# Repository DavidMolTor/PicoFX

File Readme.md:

# PICO FX

A simple stereo guitar effects platform using an RP Pico 2 development board.

## Introduction

This module is designed to be used as a development platform for guitar effects running on the RP2350 architecture.

The module contains a CS4272 codec with stereo inputs and outputs. It also includes a set of clean buffers to match the guitar and other effects in the chain.

All the power regulation is done through LDO regulators that prioritize low ripple in exchange for worse efficiency.

It is designed to work with 9V intput voltage. It also has a set of headers for it to be able to interface with a control board in the future.

## Features

 - Clear separation between digital and analog sections.

 - Steareo input and output.

 - Clean voltage delivery.

 - Flexible interface for controls.

 - Easy future development.

 - Afforable BOM.

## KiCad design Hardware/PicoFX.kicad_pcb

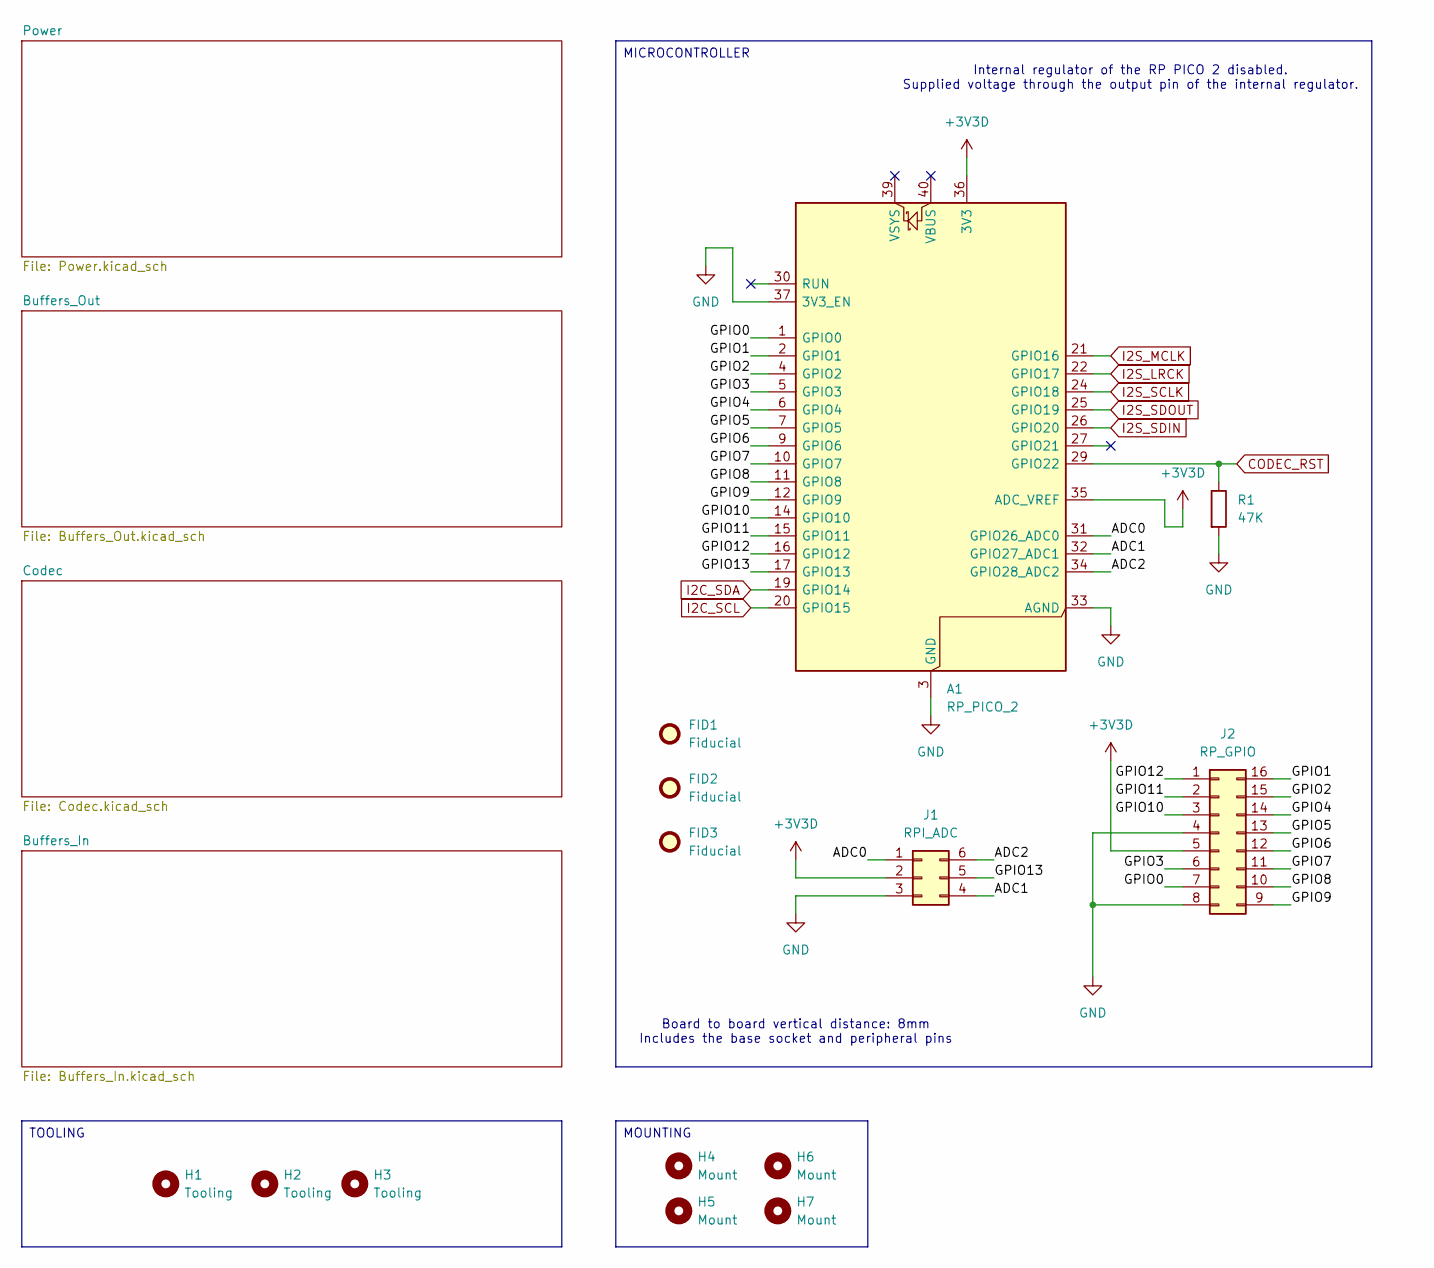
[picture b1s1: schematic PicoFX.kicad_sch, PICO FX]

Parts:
A1: RP_PICO_2; RP_PICO_2_SMD; Manufacturer Part Pico 2; JLCPCB Part C41407547
FID1, FID2, FID3: Fiducial; Fiducial_0.75mm_Mask1.5mm
H1, H2, H3: Tooling; ToolingHole_1.152mm
H4, H5, H6, H7: Mount; MountingHole_2.2mm_M2
J1: RPI_ADC; HEADER_THROUGH_2x03_P2.54mm; Manufacturer Part HC-PM254-5.0H-2x3PS-02A; JLCPCB Part C42163131
J2: RP_GPIO; HEADER_THROUGH_2x08_P2.54mm; Manufacturer Part HC-PM254-5.0H-2x8PS; JLCPCB Part C42163136
R1: 47K; R_0603_1608Metric; Manufacturer Part 0603WAF4702T5E; JLCPCB Part C25819

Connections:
+3V3D: A1.35 (ADC_VREF), A1.36 (3V3), J1.2, J2.5; also elsewhere on the board
/ADC0: A1.31 (GPIO26_ADC0), J1.1
/ADC1: A1.32 (GPIO27_ADC1), J1.4
/ADC2: A1.34 (GPIO28_ADC2), J1.6
/GPIO0: A1.1 (GPIO0), J2.7
/GPIO1: A1.2 (GPIO1), J2.16
/GPIO2: A1.4 (GPIO2), J2.15
/GPIO3: A1.5 (GPIO3), J2.6
/GPIO4: A1.6 (GPIO4), J2.14
/GPIO5: A1.7 (GPIO5), J2.13
/GPIO6: A1.9 (GPIO6), J2.12
/GPIO7: A1.10 (GPIO7), J2.11
/GPIO8: A1.11 (GPIO8), J2.10
/GPIO9: A1.12 (GPIO9), J2.9
/GPIO10: A1.14 (GPIO10), J2.3
/GPIO11: A1.15 (GPIO11), J2.2
/GPIO12: A1.16 (GPIO12), J2.1
/GPIO13: A1.17 (GPIO13), J1.5
CODEC_RST: A1.29 (GPIO22), R1.1; also elsewhere on the board
GND: A1.3 (GND), A1.8 (GND), A1.13 (GND), A1.18 (GND), A1.23 (GND), A1.28 (GND), A1.33 (AGND), A1.37 (3V3_EN), A1.38 (GND), J1.3, J2.4, J2.8, R1.2; also elsewhere on the board
I2C_SCL: A1.20 (GPIO15); also elsewhere on the board
I2C_SDA: A1.19 (GPIO14); also elsewhere on the board
I2S_LRCK: A1.22 (GPIO17); also elsewhere on the board
I2S_MCLK: A1.21 (GPIO16); also elsewhere on the board
I2S_SCLK: A1.24 (GPIO18); also elsewhere on the board
I2S_SDIN: A1.26 (GPIO20); also elsewhere on the board
I2S_SDOUT: A1.25 (GPIO19); also elsewhere on the board

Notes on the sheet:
Board to board vertical distance: 8mm Includes the base socket and peripheral pins
Internal regulator of the RP PICO 2 disabled. Supplied voltage through the output pin of the internal regulator.
MICROCONTROLLER
TOOLING
MOUNTING

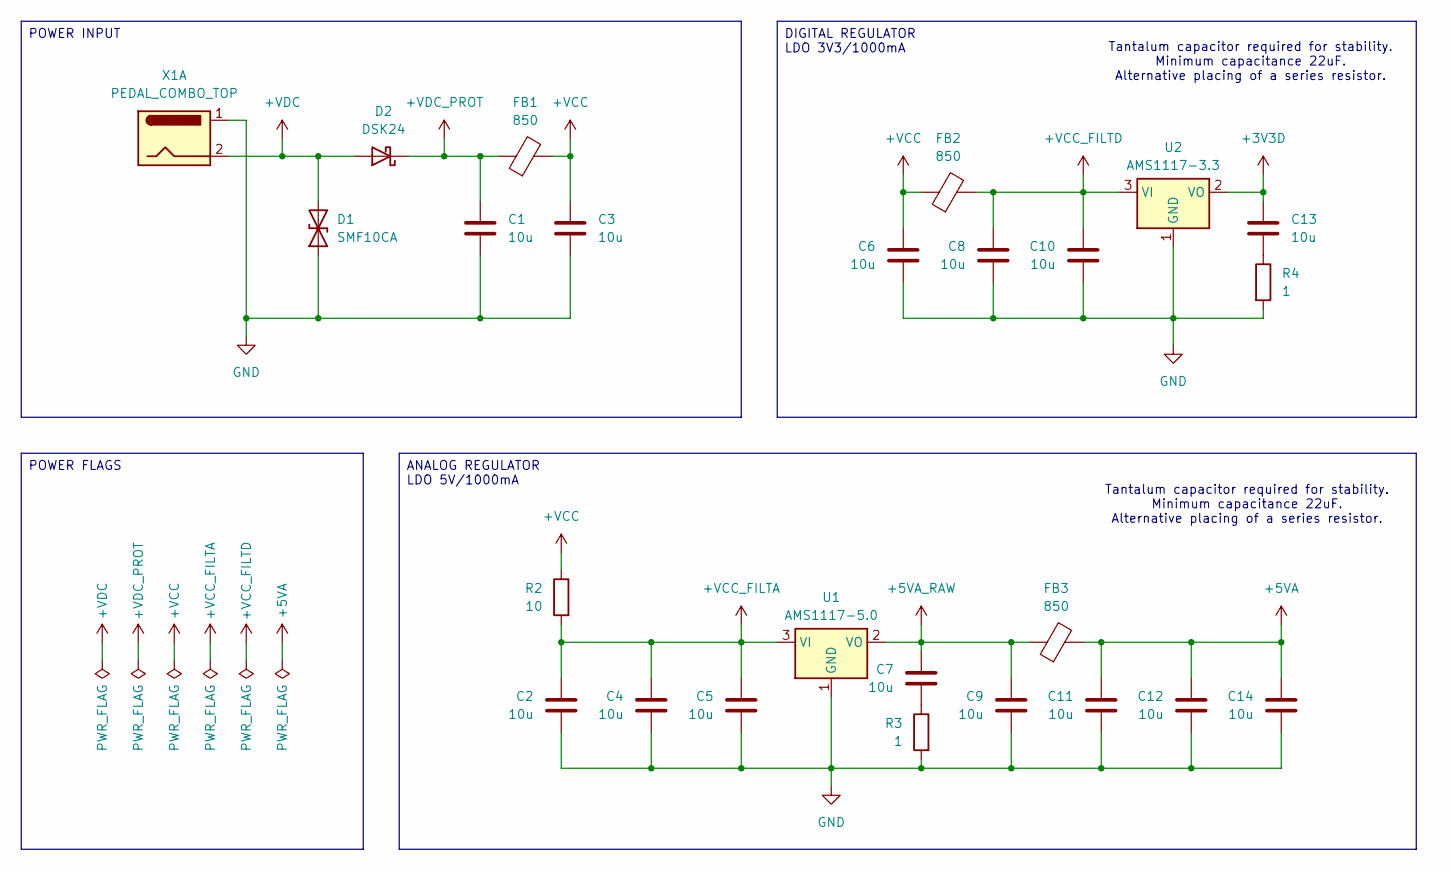
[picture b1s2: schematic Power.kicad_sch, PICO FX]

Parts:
C1, C2, C3, C4, C5, C6, C7, C8, C9, C10, C11, C12, C13, C14: 10u; C_0805_2012Metric; Manufacturer Part CL21A106KAYNNNE; JLCPCB Part C15850
D1: SMF10CA; D_SOD-123F; Manufacturer Part SMF10CA; JLCPCB Part C19077505
D2: DSK24; D_SOD-123F; Manufacturer Part DSK24; JLCPCB Part C22466352
FB1, FB2, FB3: 850; L_0603_1608Metric; Manufacturer Part SDCL1608C68NJTDF; JLCPCB Part C13415
R2: 10; R_0603_1608Metric; Manufacturer Part 0603WAF100JT5E; JLCPCB Part C22859
R3, R4: 1; R_0603_1608Metric; Manufacturer Part 0603WAF100KT5E; JLCPCB Part C22936
U1: AMS1117-5.0; SOT-223-3_TabPin2; Manufacturer Part AMS1117-5.0; JLCPCB Part C6187
U2: AMS1117-3.3; SOT-223-3_TabPin2; Manufacturer Part AMS1117-3.3; JLCPCB Part C6186
X1: PEDAL_COMBO_TOP

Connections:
+3V3D: C13.1, U2.2 (VO); also elsewhere on the board
+5VA: C11.1, C12.1, C14.1, FB3.2; also elsewhere on the board
+5VA_RAW: C7.1, C9.1, FB3.1, U1.2 (VO)
+VCC: C3.1, C6.1, FB1.2, FB2.1, R2.1
+VCC_FILTA: C2.1, C4.1, C5.1, R2.2, U1.3 (VI)
+VCC_FILTD: C8.1, C10.1, FB2.2, U2.3 (VI)
+VDC: D1.2 (A2), D2.2 (A), X1.2
+VDC_PROT: C1.1, D2.1 (K), FB1.1
GND: C1.2, C2.2, C3.2, C4.2, C5.2, C6.2, C8.2, C9.2, C10.2, C11.2, C12.2, C14.2, D1.1 (A1), R3.2, R4.2, U1.1 (GND), U2.1 (GND), X1.1; also elsewhere on the board
unnamed: C7.2, R3.1
unnamed: C13.2, R4.1

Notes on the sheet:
Tantalum capacitor required for stability. Minimum capacitance 22uF. Alternative placing of a series resistor.
DIGITAL REGULATOR LDO 3V3/1000mA
POWER INPUT
ANALOG REGULATOR LDO 5V/1000mA
POWER FLAGS

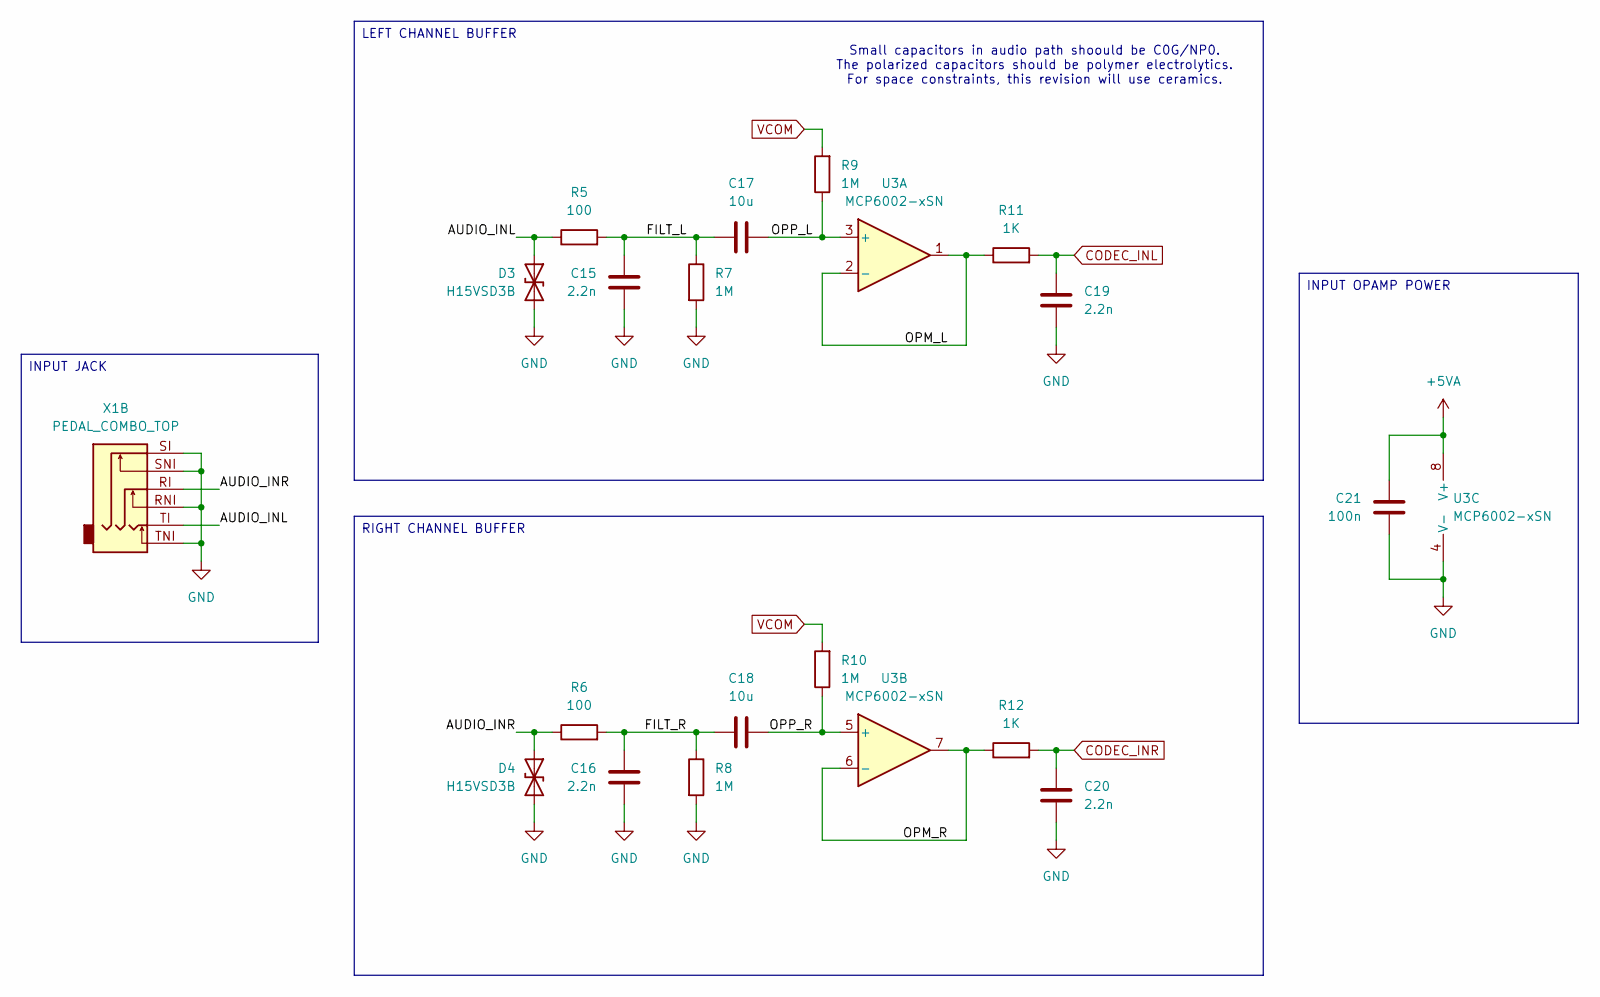
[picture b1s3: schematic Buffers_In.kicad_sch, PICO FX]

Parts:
C15, C16, C19, C20: 2.2n; C_0805_2012Metric; Manufacturer Part CL21C222JBFNNNE; JLCPCB Part C28260
C17, C18: 10u; C_0805_2012Metric; Manufacturer Part CL21A106KAYNNNE; JLCPCB Part C15850
C21: 100n; C_0603_1608Metric; Manufacturer Part CC0603KRX7R9BB104; JLCPCB Part C14663
D3, D4: H15VSD3B; D_SOD-323; Manufacturer Part H15VSD3B; JLCPCB Part C20615814
R5, R6: 100; R_0603_1608Metric; Manufacturer Part 0603WAF1000T5E; JLCPCB Part C22775
R7, R8, R9, R10: 1M; R_0603_1608Metric; Manufacturer Part 0603WAF1004T5E; JLCPCB Part C22935
R11, R12: 1K; R_0603_1608Metric; Manufacturer Part 0603WAF1001T5E; JLCPCB Part C21190
U3: MCP6002-xSN; SOIC-8_3.9x4.9mm_P1.27mm; Manufacturer Part MCP6002T-I/SN; JLCPCB Part C7377
X1: PEDAL_COMBO_TOP

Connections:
+5VA: C21.1, U3.8 (V+); also elsewhere on the board
/Buffers_In/AUDIO_INL: D3.1 (A1), R5.1, X1.TI
/Buffers_In/AUDIO_INR: D4.1 (A1), R6.1, X1.RI
/Buffers_In/FILT_L: C15.2, C17.1, R5.2, R7.1
/Buffers_In/FILT_R: C16.2, C18.1, R6.2, R8.1
/Buffers_In/OPM_L: R11.1, U3.1, U3.2 (-)
/Buffers_In/OPM_R: R12.1, U3.6 (-), U3.7
/Buffers_In/OPP_L: C17.2, R9.1, U3.3 (+)
/Buffers_In/OPP_R: C18.2, R10.1, U3.5 (+)
CODEC_INL: C19.1, R11.2; also elsewhere on the board
CODEC_INR: C20.1, R12.2; also elsewhere on the board
GND: C15.1, C16.1, C19.2, C20.2, C21.2, D3.2 (A2), D4.2 (A2), R7.2, R8.2, U3.4 (V-), X1.RNI, X1.SI, X1.SNI, X1.TNI; also elsewhere on the board
VCOM: R9.2, R10.2; also elsewhere on the board

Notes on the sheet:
Small capacitors in audio path shoould be C0G/NP0. The polarized capacitors should be polymer electrolytics. For space constraints, this revision will use ceramics.
LEFT CHANNEL BUFFER
INPUT OPAMP POWER
INPUT JACK
RIGHT CHANNEL BUFFER

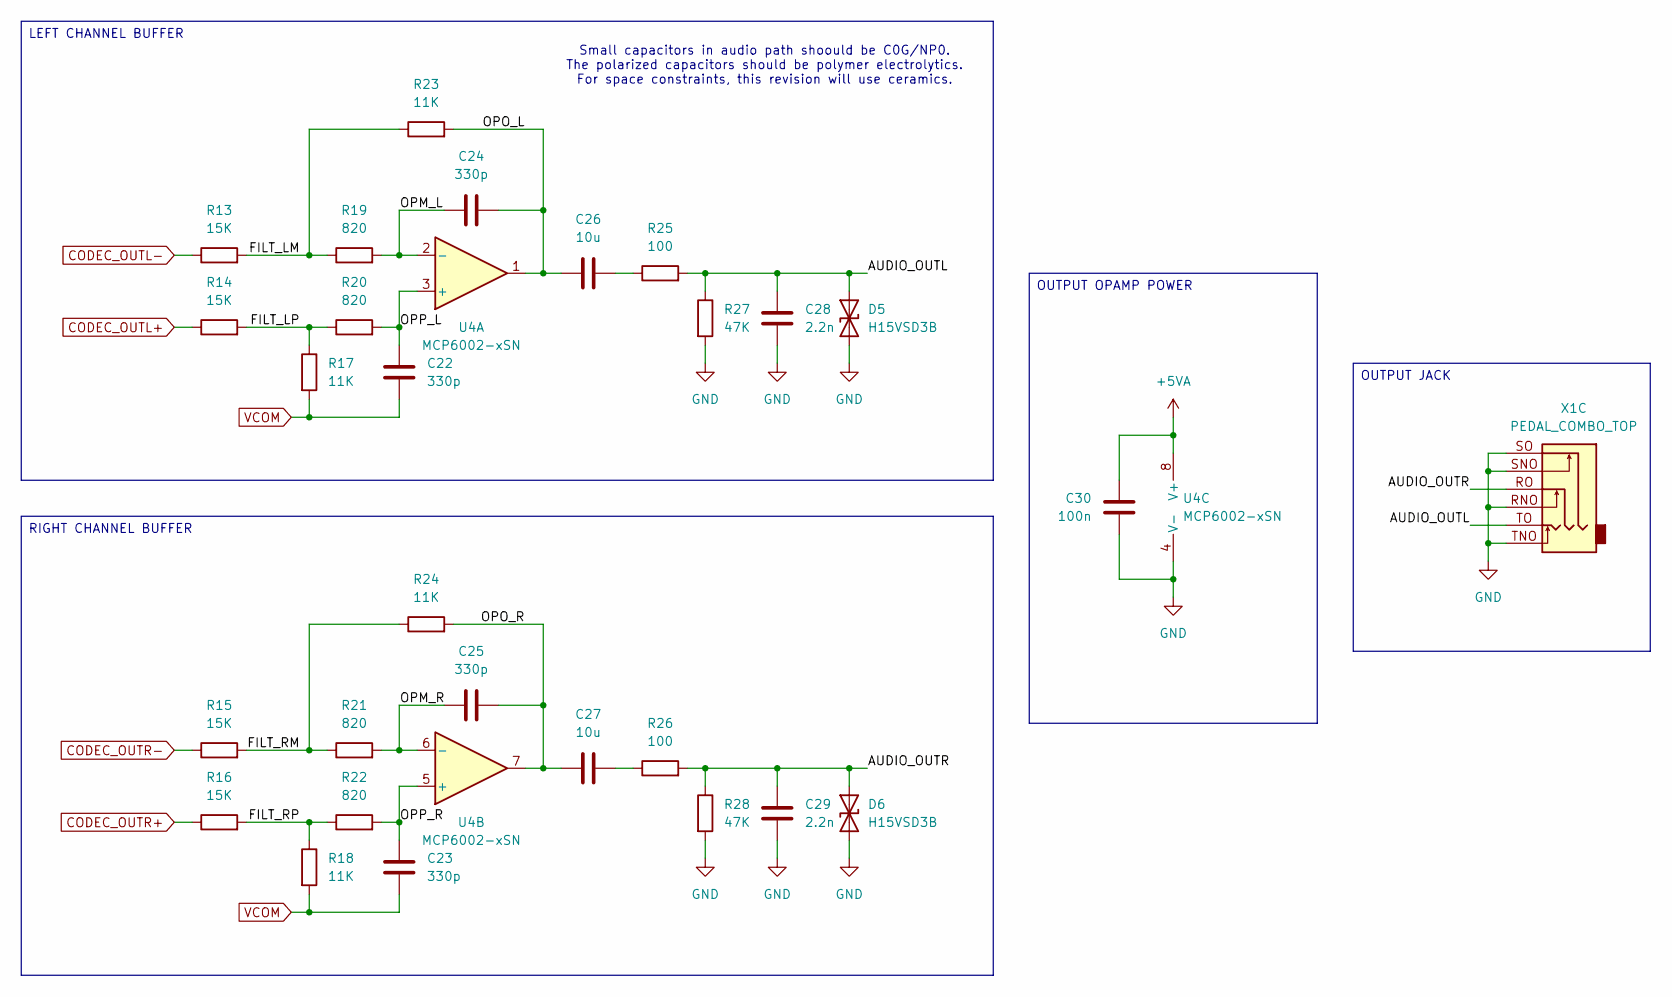
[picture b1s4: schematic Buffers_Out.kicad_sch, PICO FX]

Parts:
C22, C23, C24, C25: 330p; C_0603_1608Metric; Manufacturer Part CL10C331JB8NNNC; JLCPCB Part C1664
C26, C27: 10u; C_0805_2012Metric; Manufacturer Part CL21A106KAYNNNE; JLCPCB Part C15850
C28, C29: 2.2n; C_0805_2012Metric; Manufacturer Part CL21C222JBFNNNE; JLCPCB Part C28260
C30: 100n; C_0603_1608Metric; Manufacturer Part CC0603KRX7R9BB104; JLCPCB Part C14663
D5, D6: H15VSD3B; D_SOD-323; Manufacturer Part H15VSD3B; JLCPCB Part C20615814
R13, R14, R15, R16: 15K; R_0603_1608Metric; Manufacturer Part 0603WAF1502T5E; JLCPCB Part C22809
R17, R18, R23, R24: 11K; R_0603_1608Metric; Manufacturer Part 0603WAF1102T5E; JLCPCB Part C25950
R19, R20, R21, R22: 820; R_0603_1608Metric; Manufacturer Part 0603WAF8200T5E; JLCPCB Part C23253
R25, R26: 100; R_0603_1608Metric; Manufacturer Part 0603WAF1000T5E; JLCPCB Part C22775
R27, R28: 47K; R_0603_1608Metric; Manufacturer Part 0603WAF4702T5E; JLCPCB Part C25819
U4: MCP6002-xSN; SOIC-8_3.9x4.9mm_P1.27mm; Manufacturer Part MCP6002T-I/SN; JLCPCB Part C7377
X1: PEDAL_COMBO_TOP

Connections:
+5VA: C30.1, U4.8 (V+); also elsewhere on the board
/Buffers_Out/AUDIO_OUTL: C28.1, D5.1 (A1), R25.2, R27.1, X1.TO
/Buffers_Out/AUDIO_OUTR: C29.1, D6.1 (A1), R26.2, R28.1, X1.RO
/Buffers_Out/FILT_LM: R13.2, R19.1, R23.1
/Buffers_Out/FILT_LP: R14.2, R17.1, R20.1
/Buffers_Out/FILT_RM: R15.2, R21.1, R24.1
/Buffers_Out/FILT_RP: R16.2, R18.1, R22.1
/Buffers_Out/OPM_L: C24.1, R19.2, U4.2 (-)
/Buffers_Out/OPM_R: C25.1, R21.2, U4.6 (-)
/Buffers_Out/OPO_L: C24.2, C26.1, R23.2, U4.1
/Buffers_Out/OPO_R: C25.2, C27.1, R24.2, U4.7
/Buffers_Out/OPP_L: C22.1, R20.2, U4.3 (+)
/Buffers_Out/OPP_R: C23.1, R22.2, U4.5 (+)
CODEC_OUTL+: R14.1; also elsewhere on the board
CODEC_OUTL-: R13.1; also elsewhere on the board
CODEC_OUTR+: R16.1; also elsewhere on the board
CODEC_OUTR-: R15.1; also elsewhere on the board
GND: C28.2, C29.2, C30.2, D5.2 (A2), D6.2 (A2), R27.2, R28.2, U4.4 (V-), X1.RNO, X1.SNO, X1.SO, X1.TNO; also elsewhere on the board
unnamed: C26.2, R25.1
unnamed: C27.2, R26.1
VCOM: C22.2, C23.2, R17.2, R18.2; also elsewhere on the board

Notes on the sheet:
Small capacitors in audio path shoould be C0G/NP0. The polarized capacitors should be polymer electrolytics. For space constraints, this revision will use ceramics.
OUTPUT JACK
LEFT CHANNEL BUFFER
RIGHT CHANNEL BUFFER
OUTPUT OPAMP POWER

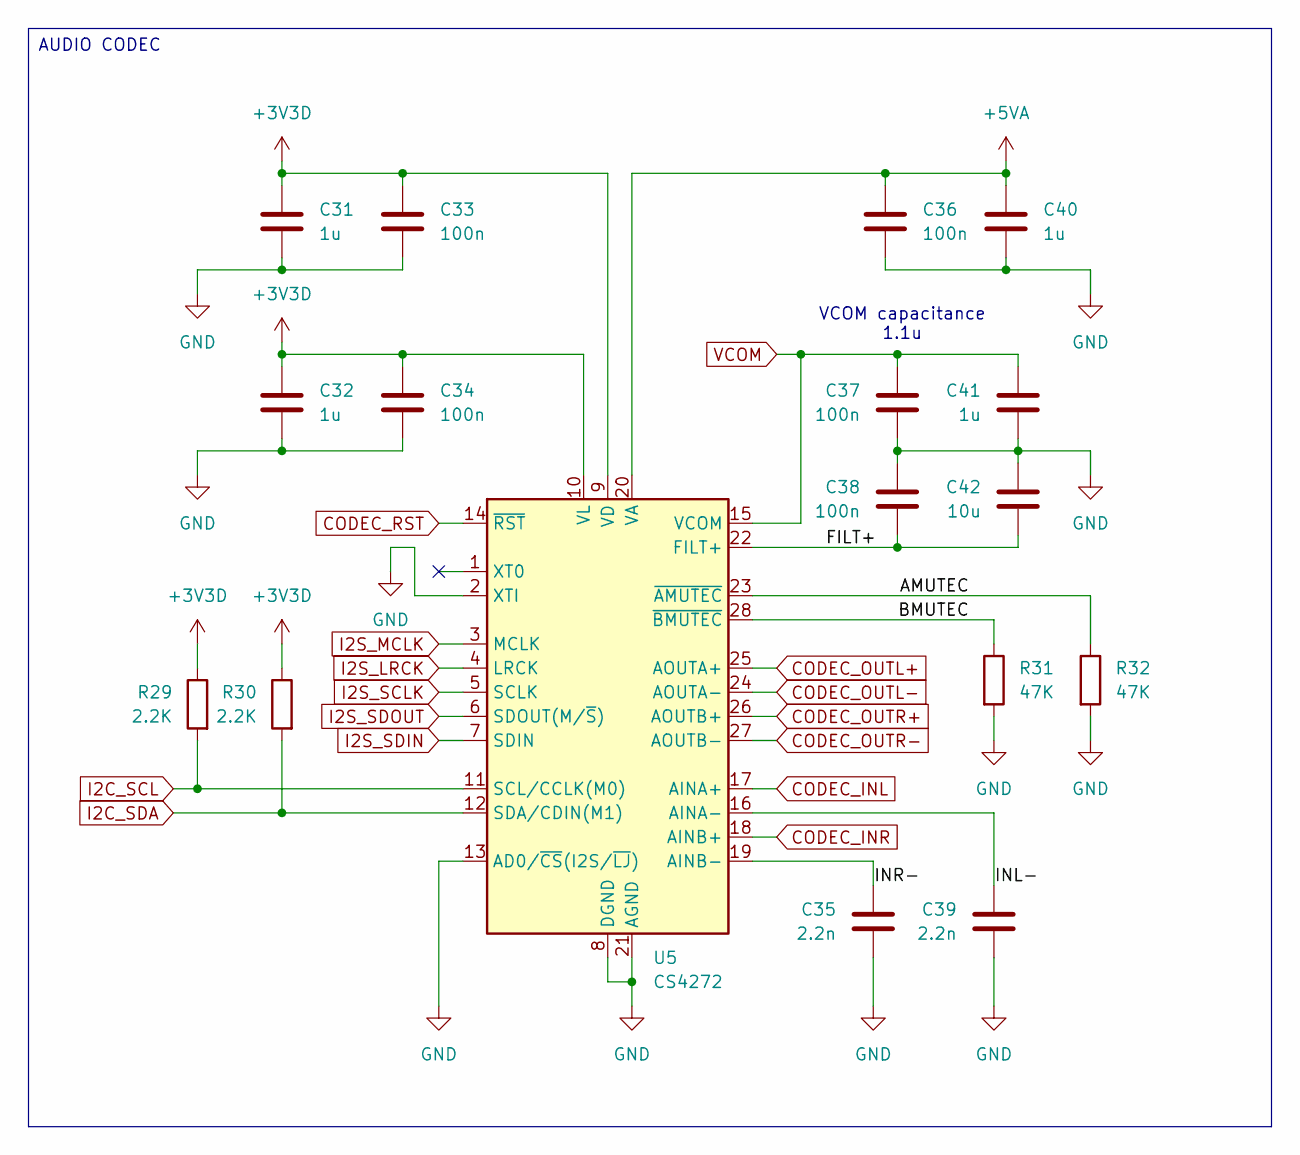
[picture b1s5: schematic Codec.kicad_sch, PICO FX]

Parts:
C31, C32, C40, C41: 1u; C_0805_2012Metric; Manufacturer Part CL21B105KBFNNNE; JLCPCB Part C28323
C33, C34, C36, C37, C38: 100n; C_0603_1608Metric; Manufacturer Part CC0603KRX7R9BB104; JLCPCB Part C14663
C35, C39: 2.2n; C_0805_2012Metric; Manufacturer Part CL21C222JBFNNNE; JLCPCB Part C28260
C42: 10u; C_0805_2012Metric; Manufacturer Part CL21A106KAYNNNE; JLCPCB Part C15850
R29, R30: 2.2K; R_0603_1608Metric; Manufacturer Part 0603WAF2201T5E; JLCPCB Part C4190
R31, R32: 47K; R_0603_1608Metric; Manufacturer Part 0603WAF4702T5E; JLCPCB Part C25819
U5: CS4272; TSSOP-28_4.4x9.7mm_P0.65mm; Manufacturer Part CS4272-CZZR; JLCPCB Part C2151111

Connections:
+3V3D: C31.2, C32.2, C33.1, C34.1, R29.1, R30.1, U5.9 (VD), U5.10 (VL); also elsewhere on the board
+5VA: C36.2, C40.1, U5.20 (VA); also elsewhere on the board
/Codec/AMUTEC: R32.1, U5.23 (~AMUTEC)
/Codec/BMUTEC: R31.1, U5.28 (~BMUTEC)
/Codec/FILT+: C38.1, C42.2, U5.22 (FILT+)
/Codec/INL-: C39.1, U5.16 (AINA-)
/Codec/INR-: C35.1, U5.19 (AINB-)
CODEC_INL: U5.17 (AINA+); also elsewhere on the board
CODEC_INR: U5.18 (AINB+); also elsewhere on the board
CODEC_OUTL+: U5.25 (AOUTA+); also elsewhere on the board
CODEC_OUTL-: U5.24 (AOUTA-); also elsewhere on the board
CODEC_OUTR+: U5.26 (AOUTB+); also elsewhere on the board
CODEC_OUTR-: U5.27 (AOUTB-); also elsewhere on the board
CODEC_RST: U5.14 (~RST); also elsewhere on the board
GND: C31.1, C32.1, C33.2, C34.2, C35.2, C36.1, C37.2, C38.2, C39.2, C40.2, C41.2, C42.1, R31.2, R32.2, U5.2 (XTI), U5.8 (DGND), U5.13 (AD0/~CS(I2S/~LJ)), U5.21 (AGND); also elsewhere on the board
I2C_SCL: R29.2, U5.11 (SCL/CCLK(M0)); also elsewhere on the board
I2C_SDA: R30.2, U5.12 (SDA/CDIN(M1)); also elsewhere on the board
I2S_LRCK: U5.4 (LRCK); also elsewhere on the board
I2S_MCLK: U5.3 (MCLK); also elsewhere on the board
I2S_SCLK: U5.5 (SCLK); also elsewhere on the board
I2S_SDIN: U5.7 (SDIN); also elsewhere on the board
I2S_SDOUT: U5.6 (SDOUT(M/~S)); also elsewhere on the board
VCOM: C37.1, C41.1, U5.15 (VCOM); also elsewhere on the board

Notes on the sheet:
VCOM capacitance 1.1u
AUDIO CODEC

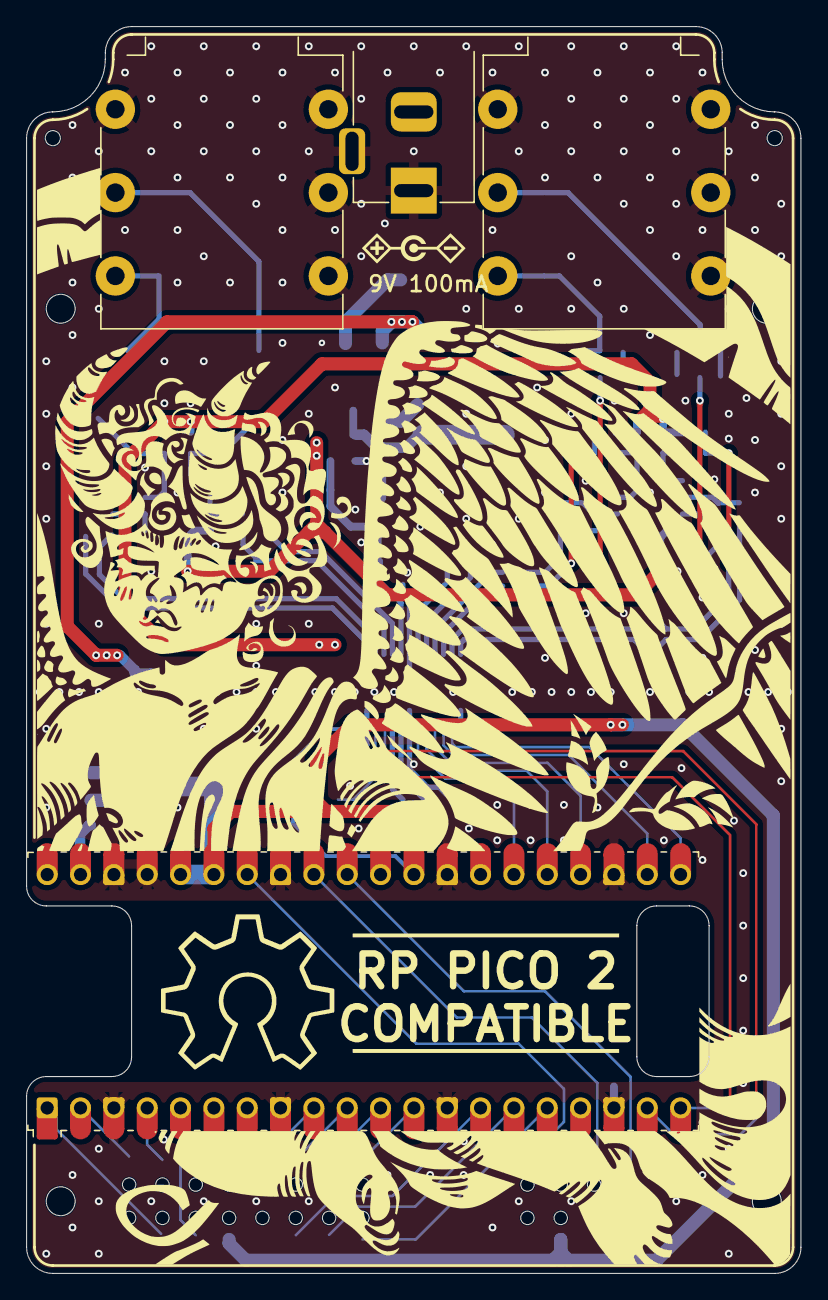
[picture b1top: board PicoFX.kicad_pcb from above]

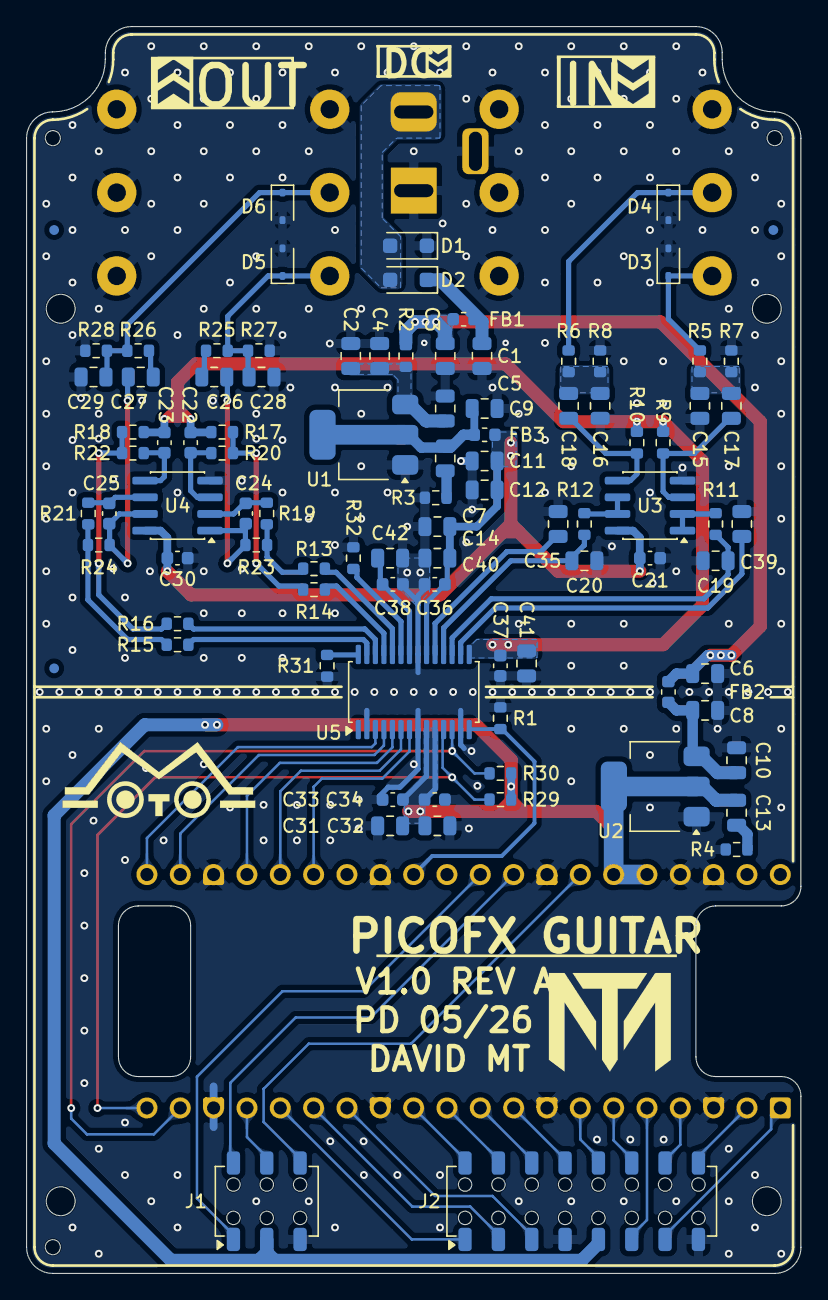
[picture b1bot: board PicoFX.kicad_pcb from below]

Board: 4 copper layers, 59.0 x 95.0 mm, 102 parts (97 on the bottom side), 70 nets.

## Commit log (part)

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2026-04-09 Initial strcture
    Added the initial project structure.
    Added the input buffer modules.
    Added the output buffer modules.
2026-04-13 Bias voltage fix
    Fixed the label for the output bias voltage.
2026-04-14 Buffer and layout
    Updated the input and output buffers.
    Updated the board layout.
2026-04-16 Layout and power supply filtering
    Updated the board layout.
    Updated the project to KiCad 10.0.
    Added additional power supply filtering.
2026-04-17 Via stitching
    Added missing vias to GND.
2026-04-21 Name update
    Updated the name of the project.
    Updated the silkscreen for the PCB layout.
2026-04-25 Layout points
    Removed unused points in layout.
2026-04-26 Layout review
    Updated the LDO layout to include a series resistor for stability.
    Updated all build files.
2026-05-23 Output files
    Updated the board silkscreen.
    Upddated the output files.
2026-05-23 Minor adjustments
    Updated the board silkscreen.
    Updated the output files.
2026-05-23 Output files
    Minor changes to the board and schematic.
    Updated the output files.
    Added a 3D model of the complete board.
2026-05-25 Assembly review
    Performed a full review of the schematic and layout.
    Minor changes to the schematic and layout.
    Updated output files.
2026-06-22 Initial software release
    Added an initial sine generator application.
    Only the I2S output is working via PIO.
